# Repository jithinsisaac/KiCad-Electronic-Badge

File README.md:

# Electronic Badge for Christmas
Herewith lies the KiCad files for an Electronic Badge made for Christmas in December 2019.

## Components used

1. OLED 128*32
1. ATTiny85
1. 0805 LEDs
1. 1206 Resistors
1. CR2032 Battery Holder 

**3D View of PCB-Front**

**3D View of PCB-Back**

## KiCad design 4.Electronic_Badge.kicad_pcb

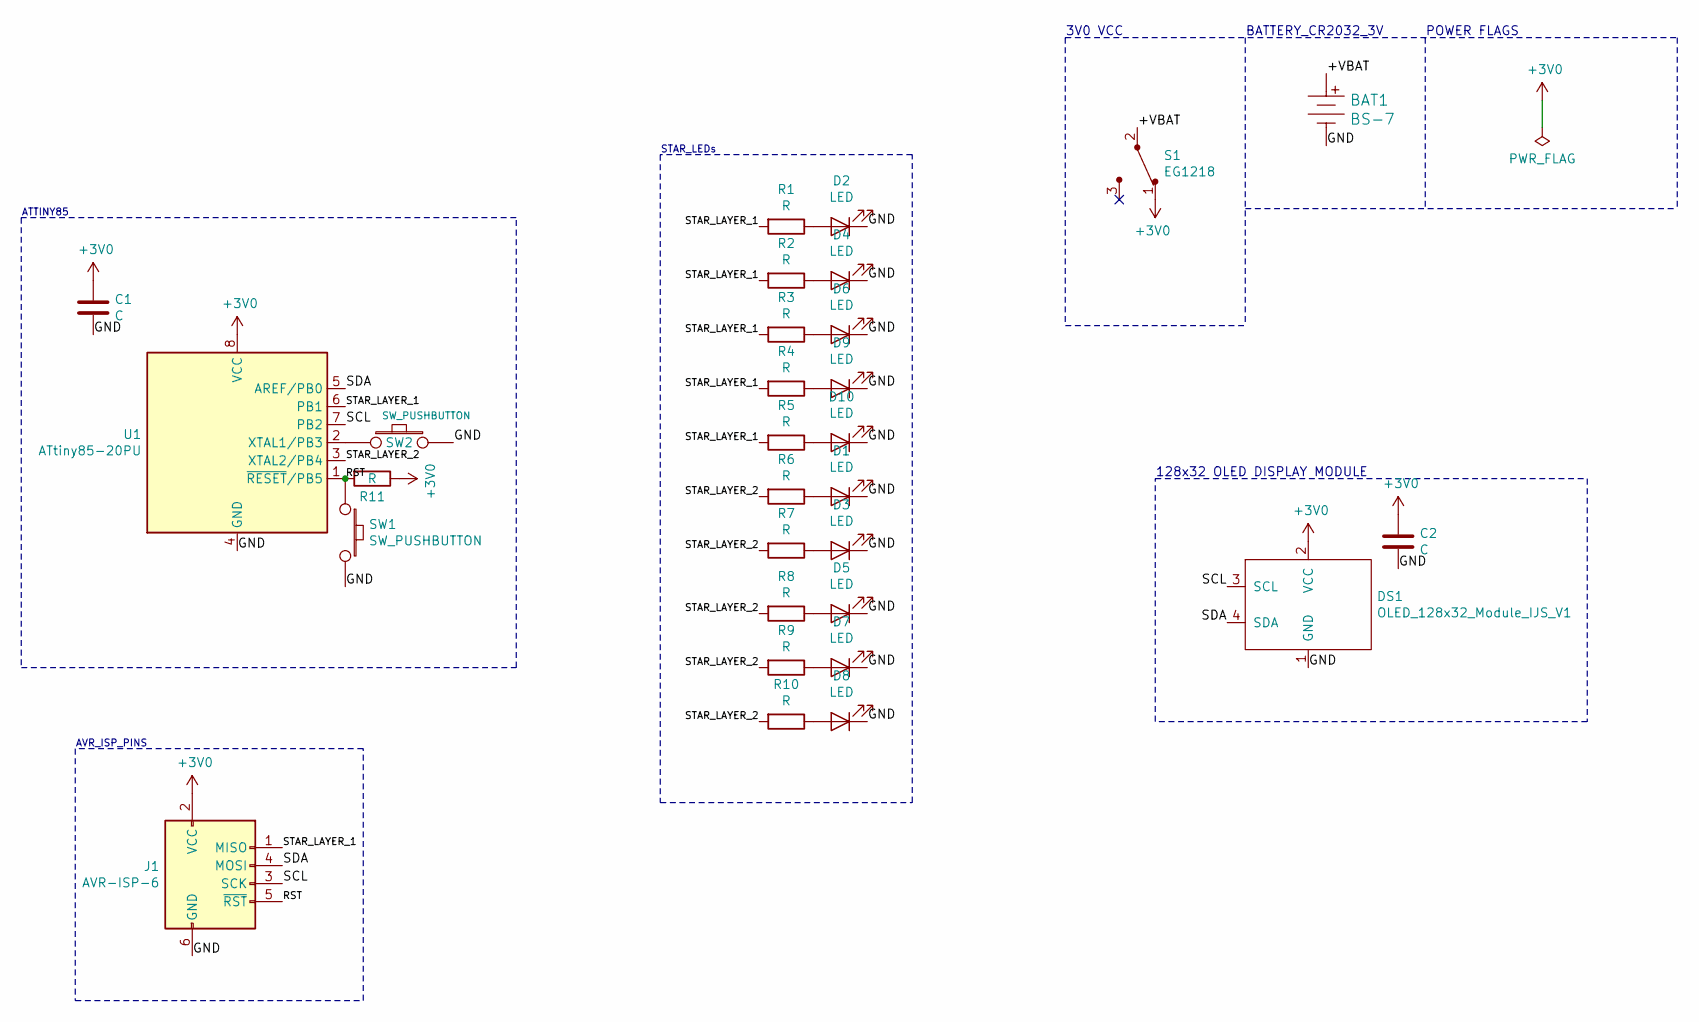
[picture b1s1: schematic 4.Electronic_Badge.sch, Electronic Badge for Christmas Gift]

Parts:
BAT1: BS-7; Battery_Holder_Coin_2032_BS-7; MPN BS-7; Digi-Key_PN BS-7-ND
C1, C2: C; C_1206_3216Metric
D1, D2, D3, D4, D5, D6, D7, D8, D9, D10: LED; LED_0805_2012Metric
DS1: OLED_128x32_Module_IJS_V1
J1: AVR-ISP-6; AVR_ISP_Pins_IJS
R1, R2, R3, R4, R5, R6, R7, R8, R9, R10, R11: R; R_1206_3216Metric
S1: EG1218; Switch_Slide_11.6x4mm_EG1218; MPN EG1218; Digi-Key_PN EG1903-ND
SW1, SW2: SW_PUSHBUTTON; SW_PUSHBUTTON_TINY_2PIN
U1: ATtiny85-20PU; DIP-8_ATTiny85_W7.62mm

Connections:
+3V0: C1.1, C2.1, DS1.2 (VCC), J1.2 (VCC), R11.1, S1.1, U1.8 (VCC)
/+VBAT: BAT1.Pos, S1.2
/GND: BAT1.Neg, C1.2, C2.2, D1.1 (K), D2.1 (K), D3.1 (K), D4.1 (K), D5.1 (K), D6.1 (K), D7.1 (K), D8.1 (K), D9.1 (K), D10.1 (K), DS1.1 (GND), J1.6 (GND), SW1.2, SW2.2, U1.4 (GND)
/RST: J1.5 (~RST), R11.2, SW1.1, U1.1 (~RESET~/PB5)
/SCL: DS1.3 (SCL), J1.3 (SCK), U1.7 (PB2)
/SDA: DS1.4 (SDA), J1.4 (MOSI), U1.5 (AREF/PB0)
/STAR_LAYER_1: J1.1 (MISO), R1.2, R2.2, R3.2, R4.2, R5.2, U1.6 (PB1)
/STAR_LAYER_2: R6.2, R7.2, R8.2, R9.2, R10.2, U1.3 (XTAL2/PB4)
unnamed: D1.2 (A), R6.1
unnamed: D2.2 (A), R1.1
unnamed: D3.2 (A), R7.1
unnamed: D4.2 (A), R2.1
unnamed: D5.2 (A), R8.1
unnamed: D6.2 (A), R3.1
unnamed: D7.2 (A), R9.1
unnamed: D8.2 (A), R10.1
unnamed: D9.2 (A), R4.1
unnamed: D10.2 (A), R5.1
unnamed: SW2.1, U1.2 (XTAL1/PB3)

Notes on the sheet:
POWER FLAGS
BATTERY_CR2032_3V
128x32 OLED DISPLAY MODULE
3V0 VCC
STAR_LEDs
ATTINY85
AVR_ISP_PINS

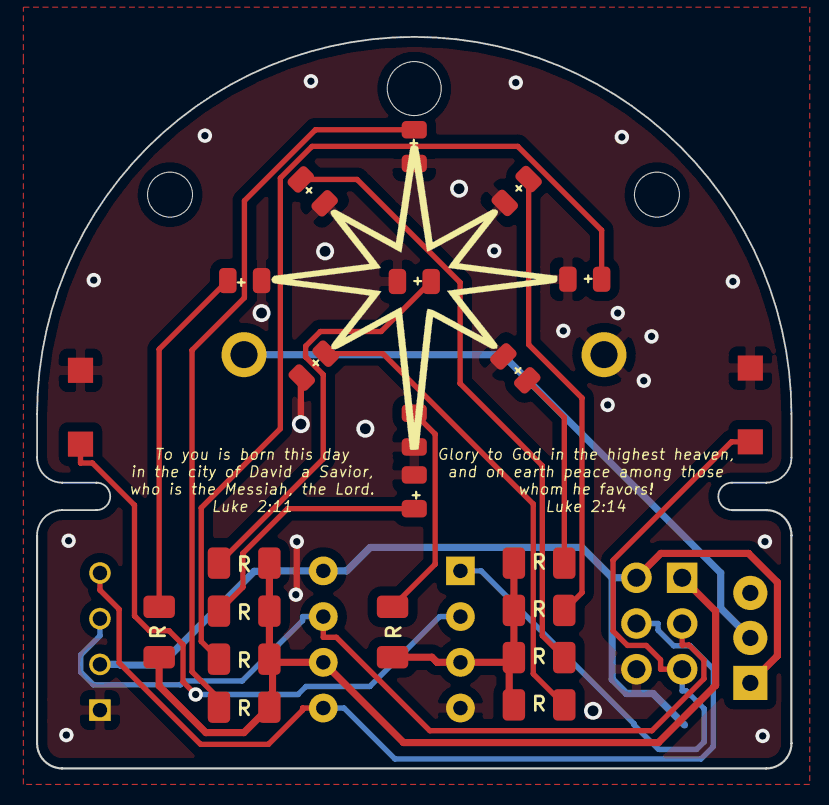
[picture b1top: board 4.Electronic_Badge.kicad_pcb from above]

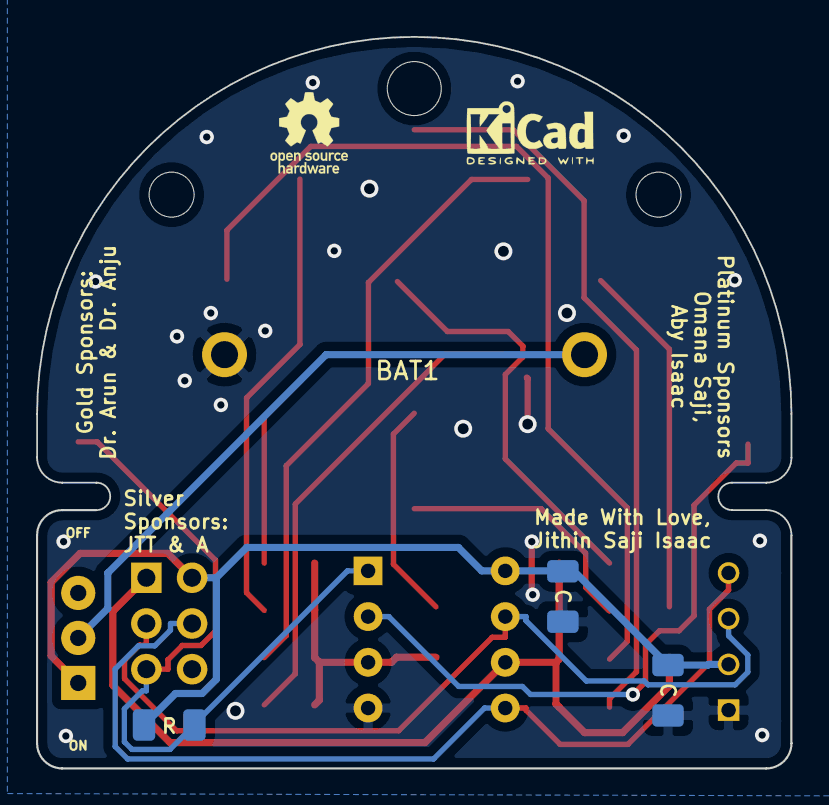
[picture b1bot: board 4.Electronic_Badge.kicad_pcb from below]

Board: 2 copper layers, 41.9 x 40.6 mm, 30 parts (7 on the bottom side), 19 nets.

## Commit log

2019-12-12 Add files via upload
    Initial upload
2019-12-12 Update README.md
    Added images to Readme
